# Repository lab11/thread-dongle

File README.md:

Thread USB Dongle
=================

This repo holds the designs for an IEEE 802.15.4 USB dongle that is compatible
with the thread networking stack and supported by [Openthread](https://github.com/openthread/openthread).
The dongle functions as an NCP mode and is compatible with the OpenThread
[Border Router](https://github.com/openthread/borderrouter).

Currently there are no readily available commercial IEEE USB Thread NCP dongles
for a reasonable cost. This dongle is designed to be inexpensive, consists of
only a USB connector, serial to UART converter, and an 802.15.4 radio SoC.

Hardware designs are located in
[hardware](https://github.com/lab11/thread-dongle/tree/master/hardware), and
firmware is located in
[software](https://github.com/lab11/thread-dongle/tree/master/software).
Firmware is based on the OpenThread NCP implementation.

To clone this repo and submodules:
```
git clone --recursive https://github.com/lab11/thread-dongle.git
```

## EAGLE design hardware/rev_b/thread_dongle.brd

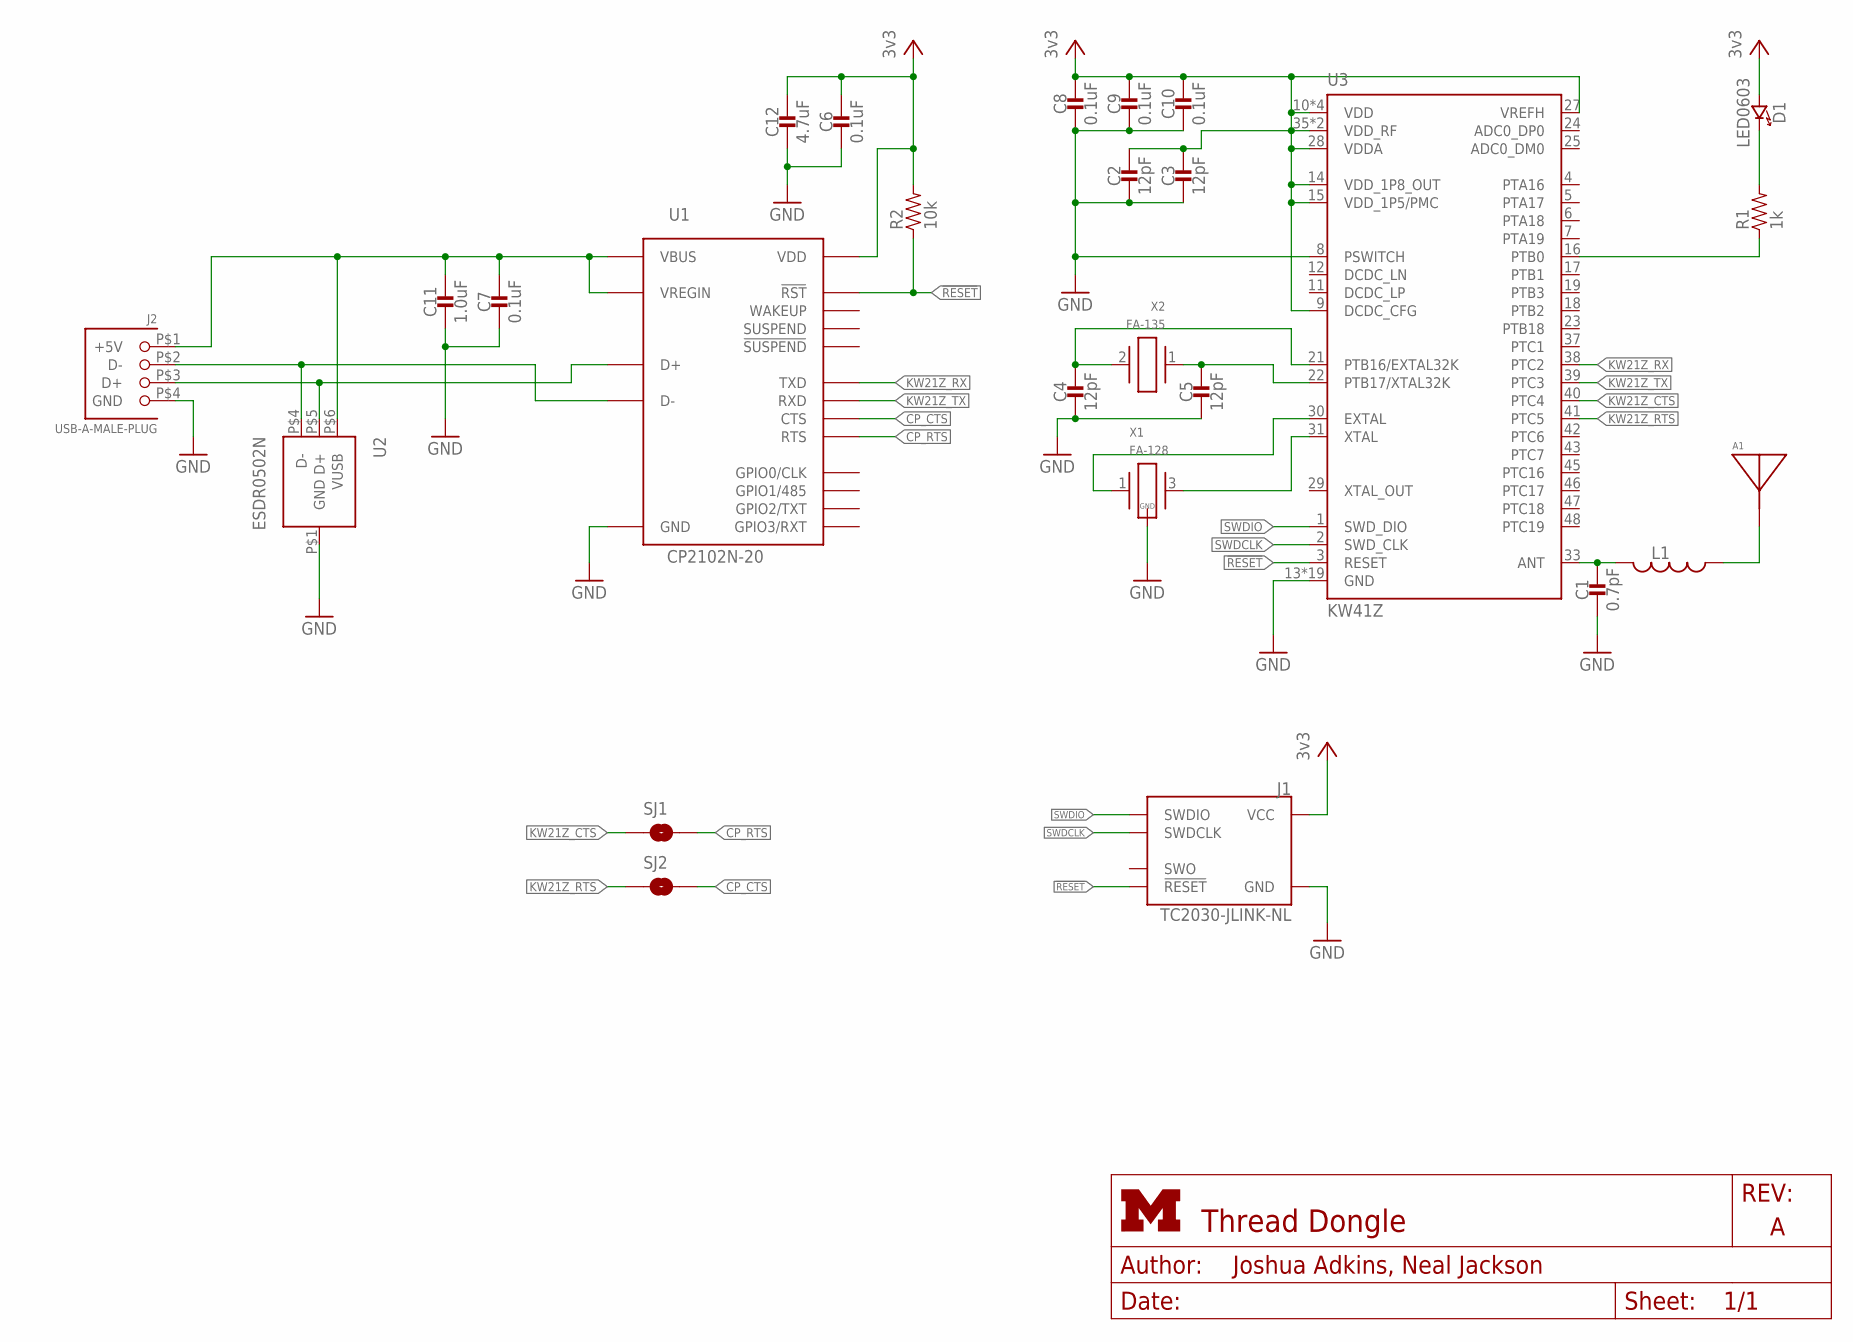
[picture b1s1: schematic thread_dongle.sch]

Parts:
A1: AH212M
C1: 0.7pF; 0402_CAP; MPN GRM1555C1HR70BA01D; DIGIKEY 490-6267-1-ND
C2, C3, C4, C5: 12pF; 0402_CAP; MPN GRM1555C1H120JA01D; DIGIKEY 490-5924-1-ND
C6, C7, C8, C9, C10: 0.1uF; 0402_CAP; MPN LMK105BJ104KV-F; DIGIKEY 587-1227-1-ND
C11: 1.0uF; 0402_CAP; MPN GRM155R61E105MA12D; DIGIKEY 490-10018-1-ND
C12: 4.7uF; 0402_CAP; MPN GRM155R60J475ME47D; DIGIKEY 490-5915-1-ND
D1: LED0603; LED-0603; MPN LTST-C194TBKT; DIGIKEY 160-1837-6-ND
J1: TC2030-JLINK-NL; TC2030-IDC-NL
J2: USB-A-MALE-PLUG; USB_A_MALE_PLUG_CUI_UP2-AH
L1: INDUCTOR0402; 0402_CAP; MPN LQG15HS5N1S02D; DIGIKEY 490-6573-1-ND
R1: 1k; 0402_RES; MPN RC0402JR-071KL; DIGIKEY 311-1.0KJRCT-ND
R2: 10k; 0402_RES; MPN RC0402JR-0710KL; DIGIKEY 311-10KJRCT-ND
SJ1, SJ2: SOLDERJUMPERNC; SJ_2S_SMALL
U1: CP2102N-20; QFN-20-3MM
U2: ESDR0502N; UDFN-6
U3: KW41Z; LAMINATE-QFN-48-7MM
X1: FA-128; MPN FA-128 32.0000MF20X-K5; DIGIKEY SER4079CT-ND
X2: FA-135; FC-135; MPN FC-135 32.7680KA-AG3; DIGIKEY SER4086CT-ND

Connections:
5V: C7.1, C11.1, J2.P$1 (+5V), U1.7 (VREGIN), U1.8 (VBUS), U2.P$6 (VUSB)
!RESET: J1.3 (!RESET), R2.1, U1.9 (!RST), U3.3 (RESET)
CP_CTS: SJ2.2, U1.15 (CTS)
CP_RTS: SJ1.2, U1.16 (RTS)
D+: J2.P$3 (D+), U1.4 (D+), U2.P$5 (D+)
D-: J2.P$2 (D-), U1.5 (D-), U2.P$4 (D-)
GND: C1.2, C2.2, C3.2, C4.2, C5.2, C6.2, C7.2, C8.2, C9.2, C10.2, C11.2, C12.2, J1.5 (GND), J2.P$4 (GND), U1.3 (GND), U1.12 (GND), U1.P$1 (GND), U2.P$1 (GND), U3.8 (PSWITCH), U3.13 (GND), U3.26 (GND), U3.34 (GND), U3.49 (GND), U3.50 (GND), U3.51 (GND), U3.52 (GND), U3.53 (GND), U3.54 (GND), U3.55 (GND), U3.56 (GND), U3.57 (GND), U3.58 (GND), U3.59 (GND), U3.60 (GND), U3.61 (GND), U3.62 (GND), U3.63 (GND), U3.64 (GND), X1.2 (GND), X1.4 (GND)
KW21Z_CTS: SJ1.1, U3.40 (PTC4)
KW21Z_RTS: SJ2.1, U3.41 (PTC5)
KW21Z_RX: U1.18 (TXD), U3.38 (PTC2)
KW21Z_TX: U1.17 (RXD), U3.39 (PTC3)
unnamed: C4.1, U3.21 (PTB16/EXTAL32K), X2.2
unnamed: C5.1, U3.22 (PTB17/XTAL32K), X2.1
unnamed: U3.31 (XTAL), X1.3 (2)
unnamed: D1.C (CATHODE), R1.2
unnamed: R1.1, U3.16 (PTB0)
unnamed: U3.30 (EXTAL), X1.1
unnamed: C1.1, L1.2, U3.33 (ANT)
unnamed: A1.P1, L1.1
SWDCLK: J1.4 (SWDCLK), U3.2 (SWD_CLK)
SWDIO: J1.2 (SWDIO), U3.1 (SWD_DIO)
VCC: C2.1, C3.1, C6.1, C8.1, C9.1, C10.1, C12.1, D1.A (ANODE), J1.1 (VCC), R2.2, U1.6 (VDD), U3.9 (DCDC_CFG), U3.10 (VDD), U3.14 (VDD_1P8_OUT), U3.15 (VDD_1P5/PMC), U3.20 (VDD), U3.27 (VREFH), U3.28 (VDDA), U3.32 (VDD), U3.35 (VDD_RF), U3.36 (VDD_RF), U3.44 (VDD)

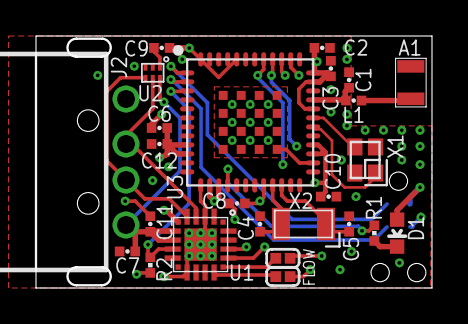
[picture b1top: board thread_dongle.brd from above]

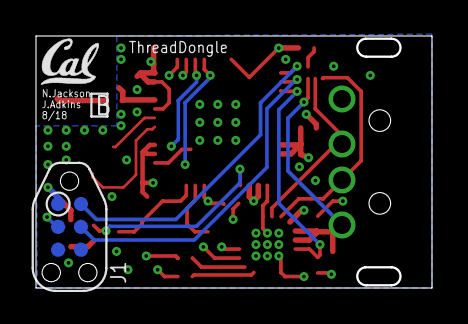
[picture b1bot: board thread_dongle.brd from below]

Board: 4 copper layers, 21.9 x 13.9 mm, 27 parts (2 on the bottom side), 22 nets.

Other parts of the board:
U$1: UCB_CAL_100MIL

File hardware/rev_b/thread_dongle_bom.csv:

# Bill of Materials,,,,,,,,,
# Converted from {},,,,,,,,,
# Generated by bom_to_text.py,,,,,,,,,
#,,,,,,,,,
,,,,,,,,,
thread_dongle,,,,,,,,,
Qty,Value,Device,Package,Parts,Description,DIGIKEY,MANUFACTURER,MPN,Notes
1,,AH212M,AH212M,A1,Small 2.4Ghz chip antenna,587-2725-1-ND,,AH212M245001-T,
1,,INDUCTOR0402,0402_CAP,L1,A very specific inductor,490-6573-1-ND,,LQG15HS5N1S02D,
5,0.1uF,CAPACITOR0402_CAP,0402_CAP,"C6, C7, C8, C9, C10",SMD Capacitor,587-1227-1-ND,,LMK105BJ104KV-F,Substitute OK
1,0.7pF,CAPACITOR0402_CAP,0402_CAP,C1,SMD Capacitor,490-6267-1-ND,,GRM1555C1HR70BA01D,Substitute OK
1,1.0uF,CAPACITOR0402_CAP,0402_CAP,C11,SMD Capacitor,490-10018-1-ND,,GRM155R61E105MA12D,Substitute OK
1,10k,RESISTOR0402_RES,0402_RES,R2,Resistor,311-10KJRCT-ND,,RC0402JR-0710KL,Substitute OK
4,12pF,CAPACITOR0402_CAP,0402_CAP,"C2, C3, C4, C5",SMD Capacitor,490-5924-1-ND,,GRM1555C1H120JA01D,Substitute OK
1,1k,RESISTOR0402_RES,0402_RES,R1,Resistor,311-1.0KJRCT-ND,,RC0402JR-071KL,Substitute OK
1,4.7uF,CAPACITOR0402_CAP,0402_CAP,C12,SMD Capacitor,490-5915-1-ND,,GRM155R60J475ME47D,Substitute OK
1,CP2102N-20,CP2102N-20,QFN-20-3MM,U1,"A cheap, simple USB to UART adapter",336-3692-ND,SiLabs,CP2102N-A01-GQFN20,
1,ESDR0502N,ESDR0502N,UDFN-6,U2,,ESDR0502NMUTBGOSCT-ND,,ESDR0502NMUTBG,
1,FA-128,FA-128,FA-128,X1,Epson MHz RANGE CRYSTAL UNIT,SER4079CT-ND,,FA-128 32.0000MF20X-K5,
1,FA-135,FA-135,FC-135,X2,Epson kHz RANGE CRYSTAL UNIT,SER4086CT-ND,,FC-135 32.7680KA-AG3,
1,KW41Z,KW41Z,LAMINATE-QFN-48-7MM,U3,NXP KW21Z Cortex M0+ 802.15.4,MKW41Z512VHT4-ND,,MKW41Z512VHT4,
1,LED0603,LED0603,LED-0603,D1,LED,160-1837-6-ND,,LTST-C194TBKT,
1,USB-A-MALE-PLUG,USB-A-MALE-PLUG,USB_A_MALE_PLUG_CUI_UP2-AH,J2,USB A Male plug connector,102-3996-ND,CUI,UP2-AH-1-TH,

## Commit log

2017-12-16 add simple readme and gitignore
2017-12-16 add some parts on schematic
2017-12-17 added routed board and schematic
2017-12-18 smaller board, cheaper uart bridge
2018-01-31 Update with KW21Z instead of SAMR21
2018-02-02 Nothing to do and no errors
2018-02-05 Fix up silkscreen
2018-03-01 ship it
2018-08-14 Rev b
    Switch to 41z, because it works
    Add pin 1 indicator for usb/uart bridge
2018-08-31 Add software + scripts to build/flash ncp
2018-09-01 Add better README, dongle photo
